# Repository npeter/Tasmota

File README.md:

Alternative firmware for [ESP8266](https://en.wikipedia.org/wiki/ESP8266) based devices with **easy configuration using webUI, OTA updates, automation using timers or rules, expandability and entirely local control over MQTT, HTTP, Serial or KNX**.
_Written for Arduino IDE and PlatformIO._

If you like **Tasmota**, give it a star, or fork it and contribute!

See [RELEASENOTES.md](RELEASENOTES.md) for release information.

In addition to the [release webpage](https://github.com/arendst/Tasmota/releases/latest) the binaries can also be downloaded from http://thehackbox.org/tasmota/release/

## Development

See [tasmota/CHANGELOG.md](tasmota/CHANGELOG.md) for detailed change information.
 
Unless your Tasmota powered device exhibits a problem or you need to make use of a feature that is not available in the Tasmota version currently installed on your device, leave your device alone - it works so don't make unnecessary changes! If the release version (i.e., the master branch) exhibits unexpected behaviour for your device and configuration, you should upgrade to the latest development version instead to see if your problem is resolved as some bugs in previous releases or development builds may already have been resolved.

The Tasmota development codebase is checked every 1-2 hours for changes. If new commits have been merged and they compile successfuly, new binary files for every variant will be posted at http://thehackbox.org/tasmota/ (this web address can be used for OTA updates too). The last compiled commit number is also indicated on the same page. It is important to note that these binaries are based on the current development codebase. These commits are tested as much as is possible and are typically quite stable. However, it is infeasible to test on the hundreds of different types of devices with all the available configuration options permitted.

Note that there is a chance, as with any upgrade, that the device may not function as expected. You must always account for the possibility that you may need to flash the device via the serial programming interface if the OTA upgrade fails. Even with the master release, you should always attempt to test the device or a similar prototype before upgrading a device which is in production or is hard to reach. And, as always, make a backup of the device configuration before beginning any firmware update.

## Disclaimer

:warning: **DANGER OF ELECTROCUTION** :warning:

If your device connects to mains electricity (AC power) there is danger of electrocution if not installed properly. If you don't know how to install it, please call an electrician (***Beware:*** certain countries prohibit installation without a licensed electrician present). Remember: _**SAFETY FIRST**_. It is not worth the risk to yourself, your family and your home if you don't know exactly what you are doing. Never tinker or try to flash a device using the serial programming interface while it is connected to MAINS ELECTRICITY (AC power).

We don't take any responsibility nor liability for using this software nor for the installation or any tips, advice, videos, etc. given by any member of this site or any related site.

## Note

Please do not ask to add new devices unless it requires additional code for new features. If the device is not listed as a module, try using [Templates](https://tasmota.github.io/docs/Templates) first. If it is not listed in the [Tasmota Device Templates Repository](http://blakadder.github.io/templates) create your own [Template](https://tasmota.github.io/docs/Templates#creating-your-template).

## Quick Install
Download one of the released binaries from https://github.com/arendst/Tasmota/releases and flash it to your hardware [using our installation guide](https://tasmota.github.io/docs/Getting-Started).

## Important User Compilation Information
If you want to compile Tasmota yourself keep in mind the following:

- Only Flash Mode **DOUT** is supported. Do not use Flash Mode DIO / QIO / QOUT as it might seem to brick your device.
- Tasmota uses a 1M linker script WITHOUT spiffs **1M (no SPIFFS)** for optimal code space.
- To make compile time changes to Tasmota use the `user_config_override.h` file. It assures keeping your custom settings when you download and compile a new version. You have to make a copy from the provided `user_config_override_sample.h` file and add your setting overrides. To enable the override you have to set a compile define as documented in the `user_config_override_sample.h` file.

## Configuration Information

Please refer to the installation and configuration articles in our [documentation](https://tasmota.github.io/docs).

## Migration Information

See [wiki migration path](https://tasmota.github.io/docs/Upgrading#migration-path) for instructions how to migrate to a major version. Pay attention to the following version breaks due to dynamic settings updates:

1. Migrate to **Sonoff-Tasmota 3.9.x**
2. Migrate to **Sonoff-Tasmota 4.x**
3. Migrate to **Sonoff-Tasmota 5.14**
4. Migrate to **Sonoff-Tasmota 6.x**
5. Migrate to **Tasmota 7.x**

--- Major change in parameter storage layout ---

6. Migrate to **Tasmota 8.1**
7. Migrate to **Tasmota 8.x**

## Support Information

For a database of supported devices see [Tasmota Device Templates Repository](https://templates.blakadder.com)

If you're looking for support on **Tasmota** there are some options available:

### Documentation

* [Documentation Site](https://tasmota.github.io/docs): For information on how to flash Tasmota, configure, use and expand it
* [FAQ and Troubleshooting](https://tasmota.github.io/docs/FAQ/): For information on common problems and solutions.
* [Commands Information](https://tasmota.github.io/docs/Commands): For information on all the commands supported by Tasmota.

### Support's Community

* [Tasmota Forum](https://groups.google.com/d/forum/sonoffusers): For usage and discussions.
* [Tasmota Support Chat](https://discord.gg/Ks2Kzd4): For support, troubleshooting and general questions. You have better chances to get fast answers from members of the Tasmota Community.
* [Search in Issues](https://github.com/arendst/Tasmota/issues): You might find an answer to your question by searching current or closed issues.

### Developers' Community

* [Bug Report](https://github.com/arendst/Tasmota/issues/new?template=Bug_report.md): For reporting Bugs of Tasmota Software.
* [Feature Request](https://github.com/arendst/Tasmota/issues/new?template=Feature_request.md): For requesting features/functions to Tasmota Software.
* [Troubleshooting](https://github.com/arendst/Tasmota/issues/new?template=Custom.md): As a last resort, you can open new *Troubleshooting* issue on GitHub if the solution could not be found using the other channels. Just remember: the more info you provide the more chances you'll have to get an accurate answer.
* [Issue a question](https://github.com/arendst/Tasmota/issues/new/choose): As a last resort, you can open a new *Question* issue on GitHub if the answer could not be found using the other channels. Just remember: the more info you provide the more chances you'll have to get an accurate answer.

## Contribute

You can contribute to Tasmota by
- providing Pull Requests (Features, Proof of Concepts, Language files or Fixes)
- testing new released features and report issues
- donating to acquire hardware for testing and implementing or out of gratitude
- contributing missing [documentation](https://tasmota.github.io/docs) for features and devices

## Credits

People helping to keep the show on the road:
- David Lang providing initial issue resolution and code optimizations
- Heiko Krupp for his IRSend, HTU21, SI70xx and Wemo/Hue emulation drivers
- Wiktor Schmidt for Travis CI implementation
- Thom Dietrich for PlatformIO optimizations
- Marinus van den Broek for his EspEasy groundwork
- Pete Ba for more user friendly energy monitor calibration
- Lobradov providing compile optimization tips
- Flexiti for his initial timer implementation
- reloxx13 for his [TasmoAdmin](https://github.com/reloxx13/TasmoAdmin) management tool
- Joachim Banzhaf for his TSL2561 library and driver
- Gijs Noorlander for his MHZ19, SenseAir and updated PubSubClient drivers
- Erik Montnemery for his HomeAssistant Discovery concept and many code tuning tips
- Federico Leoni for continued HomeAssistant Discovery support
- Aidan Mountford for his HSB support
- Daniel Ztolnai for his Serial Bridge implementation
- Gerhard Mutz for multiple sensor & display drivers, Sunrise/Sunset, and scripting
- Nuno Ferreira for his HC-SR04 driver
- Adrian Scillato for his (security)fixes and implementing and maintaining KNX
- Gennaro Tortone for implementing and maintaining Eastron drivers
- Raymond Mouthaan for managing Wemos Wiki information
- Norbert Richter for his [decode-config.py](https://github.com/tasmota/decode-config) tool
- Andre Thomas for providing [thehackbox](http://thehackbox.org/tasmota/) OTA support and daily development builds
- Joel Stein, digiblur and Shantur Rathore for their Tuya research and driver
- Frogmore42 for providing many issue answers
- Jason2866 for platformio support and providing many issue answers
- Blakadder for managing the new document site and providing template management
- Stephan Hadinger for refactoring light driver, enhancing HueEmulation and Zigbee support
- tmo for designing the official Tasmota logo
- Stefan Bode for his Shutter and Deep sleep drivers
- Jacek Ziółkowski for his [TDM](https://github.com/jziolkowski/tdm) management tool and [Tasmotizer](https://github.com/tasmota/tasmotizer) flashing tool
- Christian Staars for NRF24L01 and HM-10 Bluetooth sensor support
- Paul Diem for UDP Group communication support
- Jörg Schüler-Maroldt for his initial ESP32 port
- Javier Arigita for his thermostat driver
- Many more providing Tips, Wips, Pocs, PRs and Donations

## License

This program is licensed under GPL-3.0

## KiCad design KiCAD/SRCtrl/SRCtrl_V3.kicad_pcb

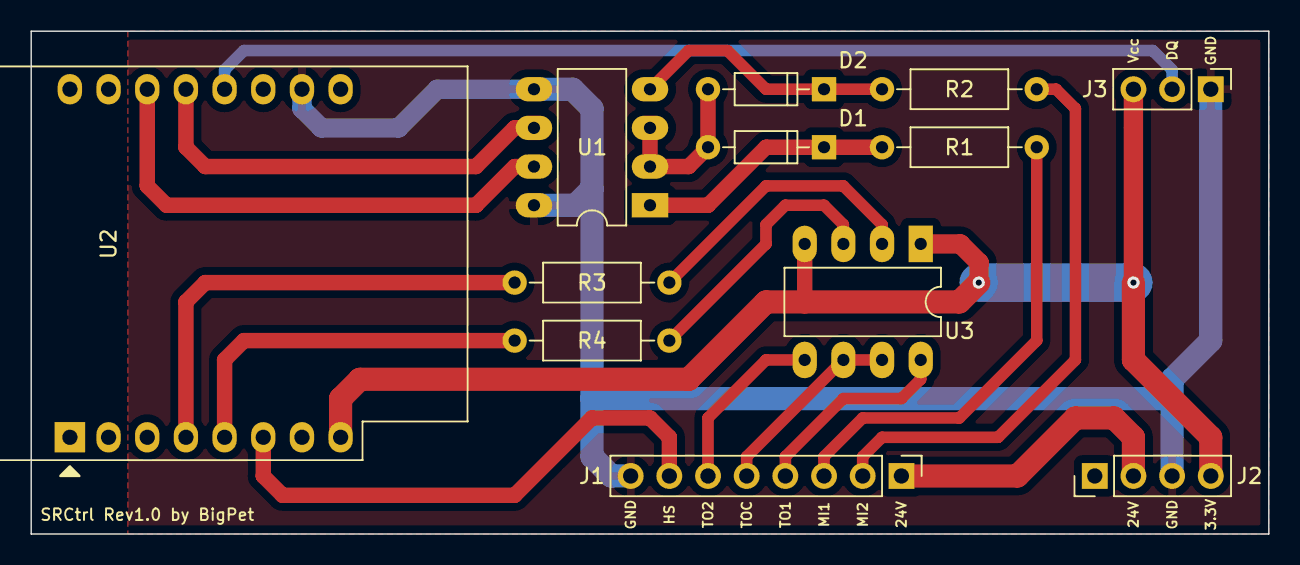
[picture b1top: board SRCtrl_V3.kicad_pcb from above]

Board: 2 copper layers, 81.3 x 33.0 mm, 12 parts (0 on the bottom side), 19 nets.

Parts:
D1, D2: BAT41; D_DO-35_SOD27_P7.62mm_Horizontal
J1: from GW60; Pin_Header_Straight_1x08_Pitch2.54mm
J2: Step-Down 24V to 3.3V; Pin_Header_Straight_1x04_Pitch2.54mm
J3: DS18x20; Pin_Header_Straight_1x03_Pitch2.54mm
R1, R2: 2k2; R_Axial_DIN0207_L6.3mm_D2.5mm_P10.16mm_Horizontal
R3, R4: 560; R_Axial_DIN0207_L6.3mm_D2.5mm_P10.16mm_Horizontal
U1, U3: TLP504A; DIP-8_W7.62mm_LongPads
U2: WeMos_D1_mini; WEMOS_D1_mini_light

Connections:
+24V: J1.1, J2.2
/DQ: J3.2, U2.12
/HallSensorIn: J1.7, U2.6
/Motor1: U1.7, U2.14
/Motor2: U1.6, U2.13
/MotorIn1: J1.3, R1.2
/MotorIn2: J1.2, R2.2
/Taster1: R3.1, U2.4
/Taster2: R4.1, U2.5
/TasterOut1: J1.4, U3.8
/TasterOut2: J1.6, U3.5
/TasterOutCom: J1.5, U3.6, U3.7
GND: J1.8, J2.3, J3.1, U1.5, U1.8, U2.10
unnamed: D1.1, R1.1, U1.1
unnamed: D1.2, D2.2, U1.2, U1.3
unnamed: D2.1, R2.1, U1.4
unnamed: R3.2, U3.2
unnamed: R4.2, U3.3
VCC: J2.4, J3.3, U2.8, U3.1, U3.4

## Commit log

2020-05-23 Test
2020-05-23 SRCtrl merged. Test OK!
2020-05-29 md issues test
